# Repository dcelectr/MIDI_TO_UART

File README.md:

# MIDI_TO_UART
A simple MIDI to UART adapter.

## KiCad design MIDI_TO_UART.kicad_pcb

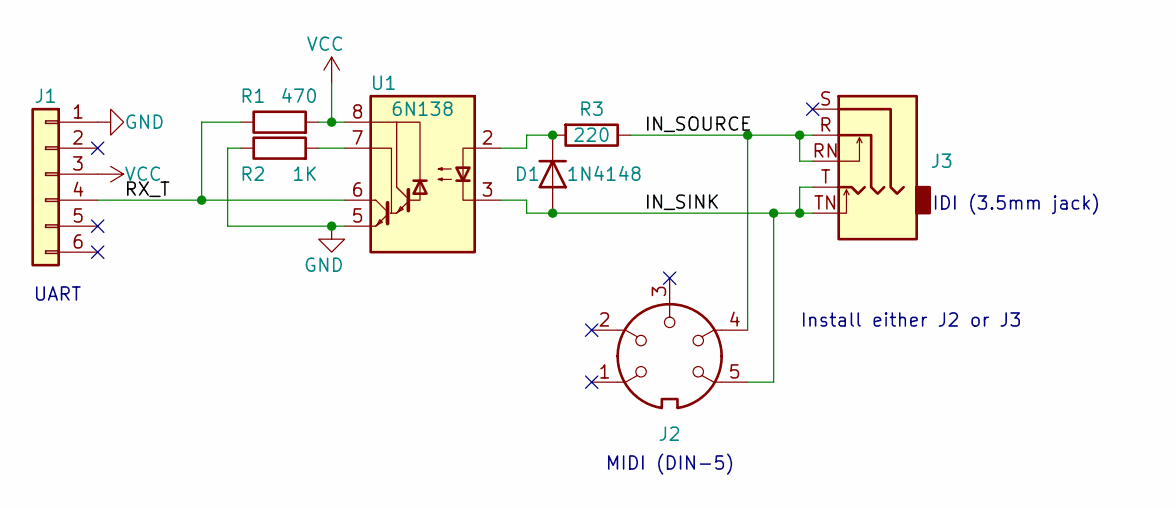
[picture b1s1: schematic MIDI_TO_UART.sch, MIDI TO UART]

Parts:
D1: 1N4148; D_DO-35_SOD27_P7.62mm_Horizontal
J1: Conn_01x06; PinSocket_1x07_P2.54mm_Horizontal
J2: DIN-5; CUI_SDS-50J
J3: AudioJack3_SwitchTR; STX3100
R1: 470; R_Axial_DIN0204_L3.6mm_D1.6mm_P7.62mm_Horizontal
R2: 1K; R_Axial_DIN0204_L3.6mm_D1.6mm_P7.62mm_Horizontal
R3: 220; R_Axial_DIN0204_L3.6mm_D1.6mm_P7.62mm_Horizontal
U1: 6N138; DIP-8_W7.62mm

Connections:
/IN_SINK: D1.2 (A), J2.5, J3.T, J3.TN, U1.3 (C2)
/IN_SOURCE: J2.4, J3.R, J3.RN, R3.1
/RX_T: J1.4, R1.1, U1.6 (VO2)
GND: J1.1, R2.1, U1.5 (GND)
unnamed: D1.1 (K), R3.2, U1.2 (C1)
unnamed: R2.2, U1.7 (VO1)
VCC: J1.3, R1.2, U1.8 (VCC)

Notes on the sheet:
Install either J2 or J3
UART
MIDI (3.5mm jack)
MIDI (DIN-5)

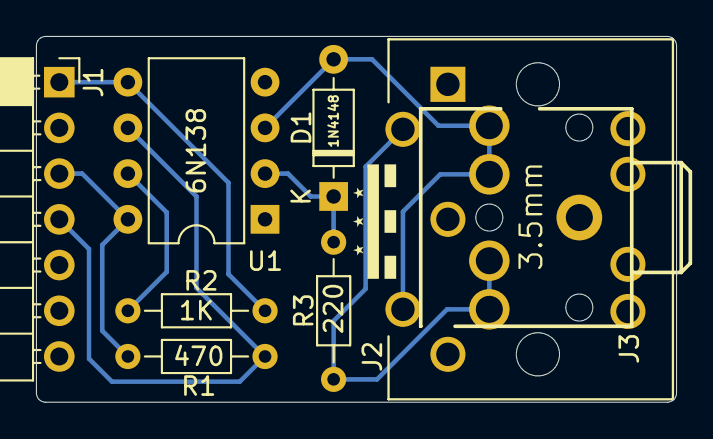
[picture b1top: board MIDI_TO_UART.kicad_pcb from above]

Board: 2 copper layers, 35.6 x 20.3 mm, 8 parts (0 on the bottom side), 7 nets.

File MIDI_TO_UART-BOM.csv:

Reference, Quantity, Value, Footprint, P/N
D1 ,1,1N4148,Diode_THT:D_DO-35_SOD27_P7.62mm_Horizontal,1N4148
J1 ,1,Conn_01x06,Connector_PinSocket_2.54mm:PinSocket_1x07_P2.54mm_Horizontal,PPPC061LGBN-RC
J2 ,1,DIN-5,User_PCB_Libraries:CUI_SDS-50J,CP-2350
J3 ,1,AudioJack3_SwitchTR,User_PCB_Libraries:STX3100,STX3100
R1 ,1,470,Resistor_THT:R_Axial_DIN0204_L3.6mm_D1.6mm_P7.62mm_Horizontal,470 Ohm 1/4 W
R2 ,1,1K,Resistor_THT:R_Axial_DIN0204_L3.6mm_D1.6mm_P7.62mm_Horizontal,1 kOhm 1/4 W
R3 ,1,220,Resistor_THT:R_Axial_DIN0204_L3.6mm_D1.6mm_P7.62mm_Horizontal,220 Ohm 1/4 W
U1 ,1,6N138,Package_DIP:DIP-8_W7.62mm,6N138
